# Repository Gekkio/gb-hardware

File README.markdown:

# Game Boy -related custom hardware by gekkio
Licensed under Creative Commons Attribution 4.0 International.

Used libraries:

* [gekkio-kicad-libs](https://github.com/Gekkio/gekkio-kicad-libs)
* [kicad-footprints](https://github.com/KiCad/kicad-footprints)
* [kicad-symbols](https://github.com/KiCad/kicad-symbols)

## License violations (a.k.a Naughty List)

All the designs in this repository are licensed very liberally under CC BY 4.0,
so you can modify and/or sell them commercially if you want. There's just one
requirement: **attribution**

Basically it just means this: don't remove the original creator's name from the
design. [Here's the full description about it in CC BY 4.0](https://creativecommons.org/licenses/by/4.0/#deed-conditions)

Known license violations:

- Ferrante Crafts: While it wasn't fully intentional and they've
  apologised, they took my GB-CART32K-A design, altered the silkscreen to
  include their name while removing all mention of mine, and then sold these
  carts to people for profit

[Don't be this meme!](https://knowyourmeme.com/memes/i-made-this)

## GB-BENCH-G1

Test bench board for 1st generation Game Boy CPUs (DMG-CPU, SGB-CPU).

* PCB size: 100x100mm
* PCB thickness: any
* Layer count: 4
* Surface finish: any

## GB-BRK-CART

Breakout Game Boy cartridge.

* PCB size: 51.4x61mm
* PCB thickness: 1.0mm
* Layer count: 2
* Surface finish: ENIG (absolutely *do not* choose HASL)

[GB-BRK-CART v4.0 Mouser project for easy part shopping](http://www.mouser.com/ProjectManager/ProjectDetail.aspx?AccessID=61700168c3)

## GB-BRK-LINK-A

Breakout board for original Game Boy (DMG) link port.

* PCB size: 30x34mm
* PCB thickness: 1.2mm
* Layer count: 2
* Surface finish: any

## GB-BRK-LINK-B

Breakout board for compact link port used in Game Boy Pocket (MGB) and later.

* PCB size: 30x34mm
* PCB thickness: 1.2mm
* Layer count: 2
* Surface finish: any

## GB-BRK-M-XS

Compact male breakout board for the Game Boy cartridge slot.

* PCB size: 51.4x25mm
* PCB thickness: 1.0mm
* Layer count: 2
* Surface finish: ENIG (absolutely *do not* choose HASL)

## GB-BRK-SLOT-A

Breakout board for original Game Boy (DMG) cartridge slot.

* PCB size: 81x80mm
* PCB thickness: 1.2mm
* Layer count: 2
* Surface finish: any

## GB-BRK-SLOT-B

Breakout board for Super Game Boy (SGB) / Super Game Boy 2 (SGB2) cartridge
slot.

* PCB size: 81x80mm
* PCB thickness: 1.2mm
* Layer count: 2
* Surface finish: any

## GB-LIVE32

32 kB ROM-only rapid development cartridge.

* PCB size: 51.4x61mm
* PCB thickness: 1.0mm
* Layer count: 4
* Surface finish: ENIG (absolutely *do not choose HASL*)

[Firmware + software](https://github.com/Gekkio/gb-live32)

[GB-LIVE32 v2.0 Mouser project for easy part shopping](https://www.mouser.com/ProjectManager/ProjectDetail.aspx?AccessID=16281c67ef)

## GB-CART32K-A

Simple ROM-only flash cartridge for 32kx8 PLCC-32 flash (larger chips up to
512kx8 are supported, but only 32k is usable).

* PCB size: 51.4x61mm
* PCB thickness: 1.0mm
* Layer count: 2
* Surface finish: ENIG (absolutely *do not choose HASL*)

## GB-CART256K-A

Simple ROM-only flash cartridge for 128kx8 / 256kx8 PLCC-32 flash.

* PCB size: 51.4x61mm
* PCB thickness: 1.0mm
* Layer count: 2
* Surface finish: ENIG (absolutely *do not choose HASL*)

[Firmware](https://github.com/Gekkio/gb-cart256k-a)

## GB-BRK-CPU-G1

Breakout board for 1st generation Game Boy CPUs (DMG/SGB).

* PCB size: 80x80mm
* PCB thickness: any
* Layer count: 2
* Surface finish: any

## GB-BRK-CPU-G2

Breakout board for 2nd generation Game Boy CPUs (MGB/SGB2).

* PCB size: 80x80mm
* PCB thickness: any
* Layer count: 2
* Surface finish: any

## GB-BRK-TR-A

Breakout board for original Game Boy (DMG) power board transformer.

* PCB size: 24x35mm
* PCB thickness: any
* Layer count: 2
* Surface finish: any

## GB-MBCTEST

Game Boy MBC (Memory Bank Controller) testing cartridge.

* PCB size: 51.4x61mm
* PCB thickness: 1.0mm
* Layer count: 2
* Surface finish: ENIG (absolutely *do not choose HASL*)

## GB-CARTPP-XC

An eXtra Cheap Game Boy cartridge dumper/flasher based on PIC18F45K50.

* PCB size: 80x55mm
* PCB thickness: any (1.0mm recommended)
* Layer count: 2
* Surface finish: any

## GB-CARTPP-DIY

A Game Boy cartridge dumper/flasher based on PIC18F45K50 with DIY-friendly
parts (big and easy to solder).

* PCB size: 100x100mm
* PCB thickness: any
* Layer count: 2
* Surface finish: any

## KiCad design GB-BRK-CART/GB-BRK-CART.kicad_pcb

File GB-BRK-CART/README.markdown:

# Notes

* The power LED (+ resistor) and the bypass capacitor are optional.
* The value of R1 might be too high to get enough current for the LED and can
  be replaced with a lower value if necessary. The value is set quite high to
  minimize power usage and still works fine with the components I use.
* All parts in the BOM can be replaced with pretty much any similar parts.

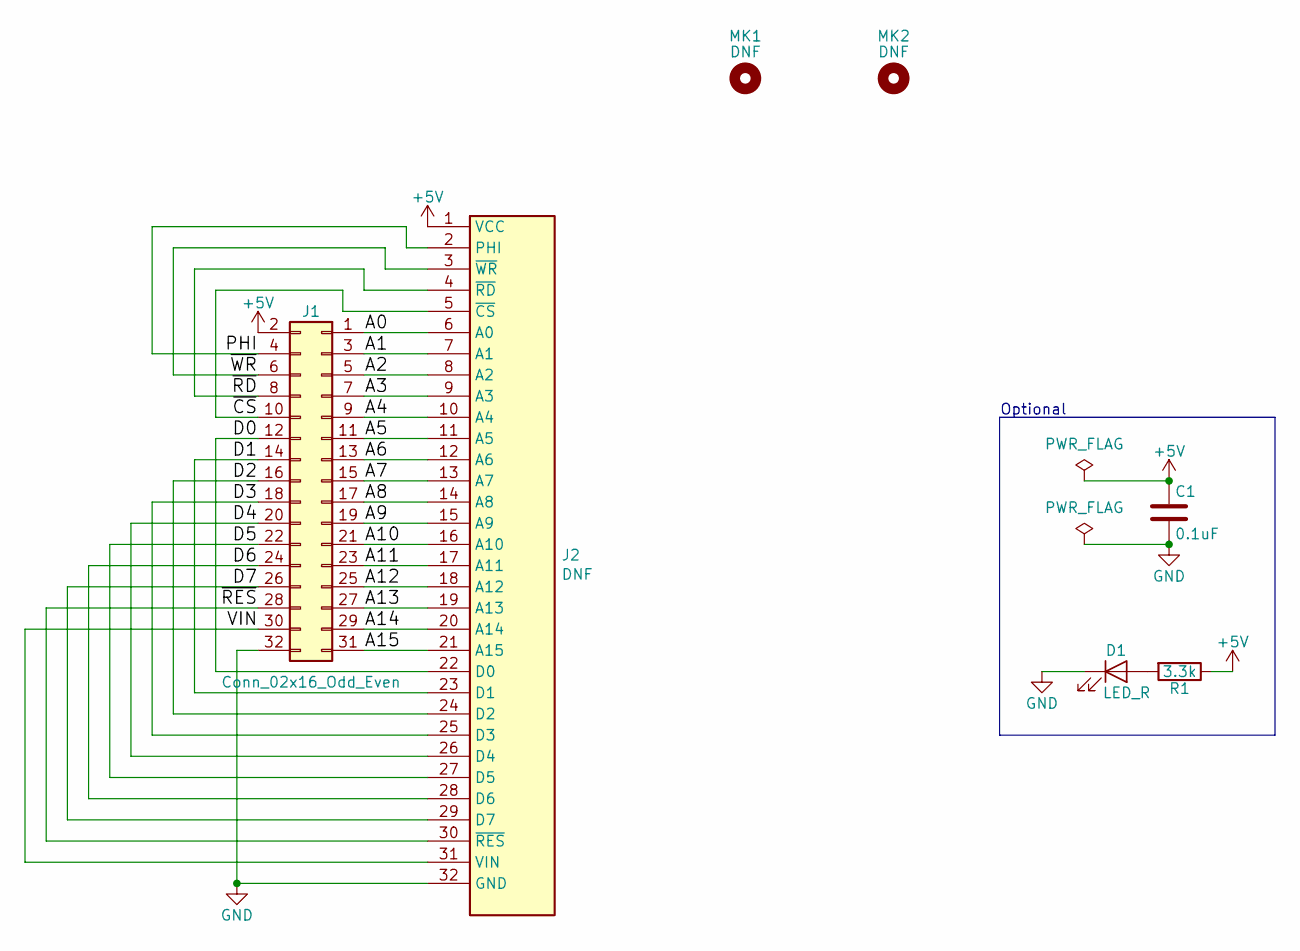
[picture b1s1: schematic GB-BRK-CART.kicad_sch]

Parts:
C1: 0.1uF; C_0603_1608Metric; Rating 16V X5R; MPN 06035C104KAT4A
D1: LED_R; LED_0603_1608Metric; MPN 150060SS75000
J1: Conn_02x16_Odd_Even; PinHeader_2x16_P2.54mm_Vertical_SMD; MPN 15-91-0800
J2: DNF; GameBoy_Cartridge_1x32_P1.50mm_Edge
MK1: DNF; MountingHole_7.2mm
MK2: DNF; MountingHole_2.3mm
R1: 3.3k; R_0603_1608Metric; Rating 1/10W 5%; MPN CRCW06033K30JNEB

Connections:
+5V: C1.1, J1.2, J2.1 (VCC), R1.1
/A0: J1.1, J2.6 (A0)
/A1: J1.3, J2.7 (A1)
/A2: J1.5, J2.8 (A2)
/A3: J1.7, J2.9 (A3)
/A4: J1.9, J2.10 (A4)
/A5: J1.11, J2.11 (A5)
/A6: J1.13, J2.12 (A6)
/A7: J1.15, J2.13 (A7)
/A8: J1.17, J2.14 (A8)
/A9: J1.19, J2.15 (A9)
/A10: J1.21, J2.16 (A10)
/A11: J1.23, J2.17 (A11)
/A12: J1.25, J2.18 (A12)
/A13: J1.27, J2.19 (A13)
/A14: J1.29, J2.20 (A14)
/A15: J1.31, J2.21 (A15)
/D0: J1.12, J2.22 (D0)
/D1: J1.14, J2.23 (D1)
/D2: J1.16, J2.24 (D2)
/D3: J1.18, J2.25 (D3)
/D4: J1.20, J2.26 (D4)
/D5: J1.22, J2.27 (D5)
/D6: J1.24, J2.28 (D6)
/D7: J1.26, J2.29 (D7)
/PHI: J1.4, J2.2 (PHI)
/VIN: J1.30, J2.31 (VIN)
/~CS: J1.10, J2.5 (~CS)
/~RD: J1.8, J2.4 (~RD)
/~RES: J1.28, J2.30 (~RES)
/~WR: J1.6, J2.3 (~WR)
GND: C1.2, D1.1 (K), J1.32, J2.32 (GND)
unnamed: D1.2 (A), R1.2

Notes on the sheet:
Optional

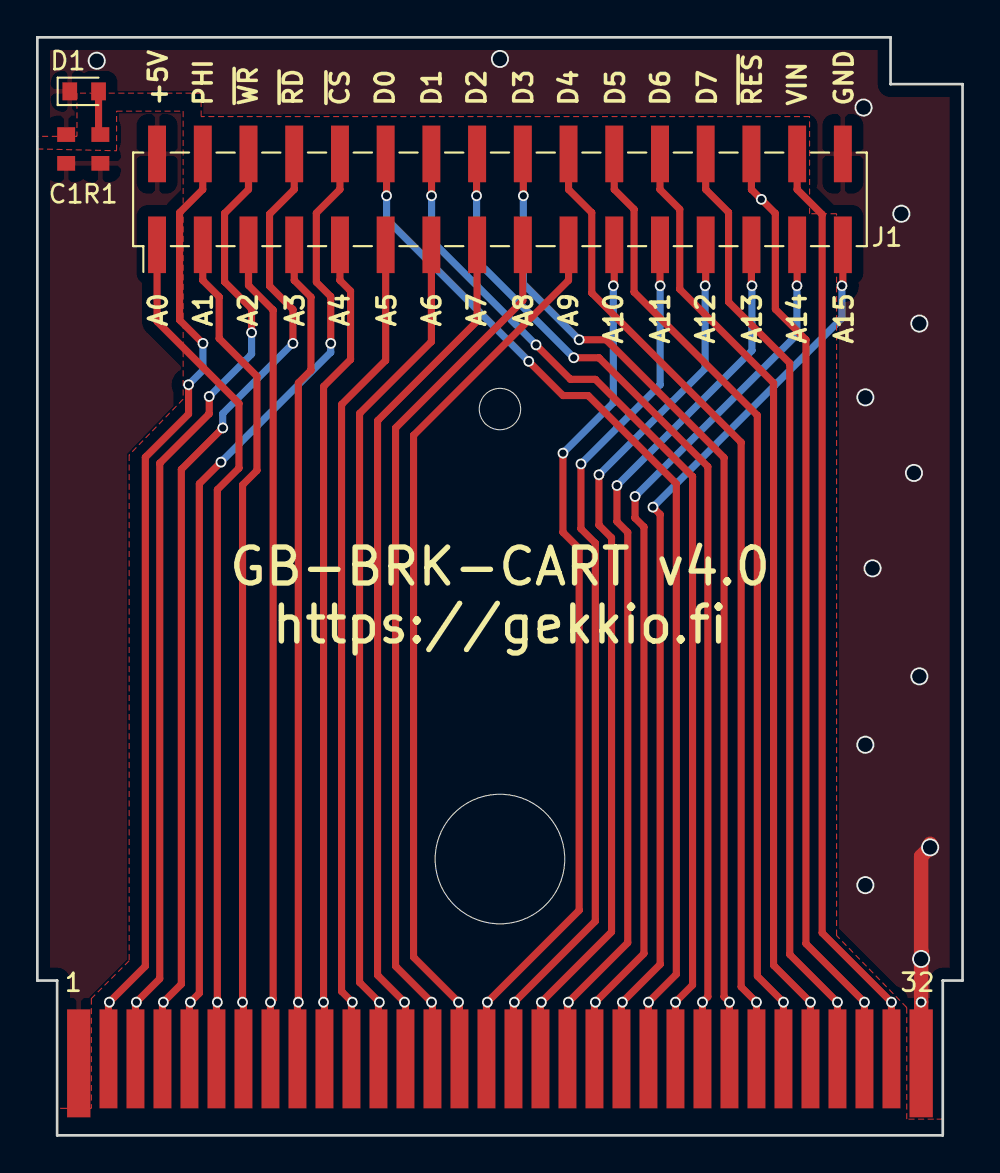
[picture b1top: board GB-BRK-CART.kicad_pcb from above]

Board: 2 copper layers, 51.4 x 61.0 mm, 7 parts (0 on the bottom side), 33 nets.

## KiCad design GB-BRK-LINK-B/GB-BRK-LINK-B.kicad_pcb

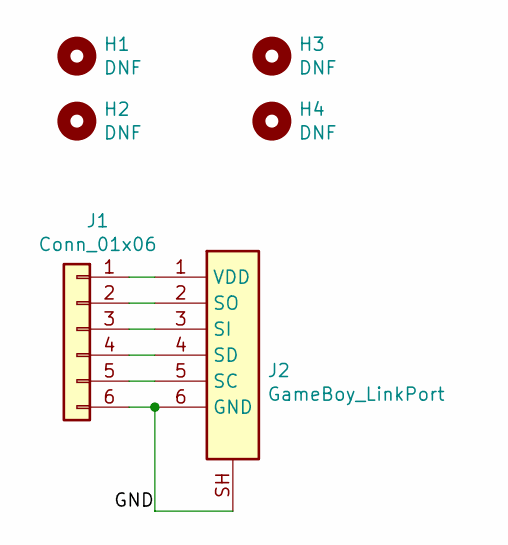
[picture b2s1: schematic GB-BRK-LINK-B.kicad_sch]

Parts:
H1, H2, H3, H4: DNF; MountingHole_3.2mm_M3
J1: Conn_01x06; PinHeader_1x06_P2.54mm_Vertical
J2: GameBoy_LinkPort; GameBoy_LinkPort_MGB_Horizontal

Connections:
/GND: J1.6, J2.6 (GND), J2.SH
unnamed: J1.1, J2.1 (VDD)
unnamed: J1.2, J2.2 (SO)
unnamed: J1.3, J2.3 (SI)
unnamed: J1.4, J2.4 (SD)
unnamed: J1.5, J2.5 (SC)

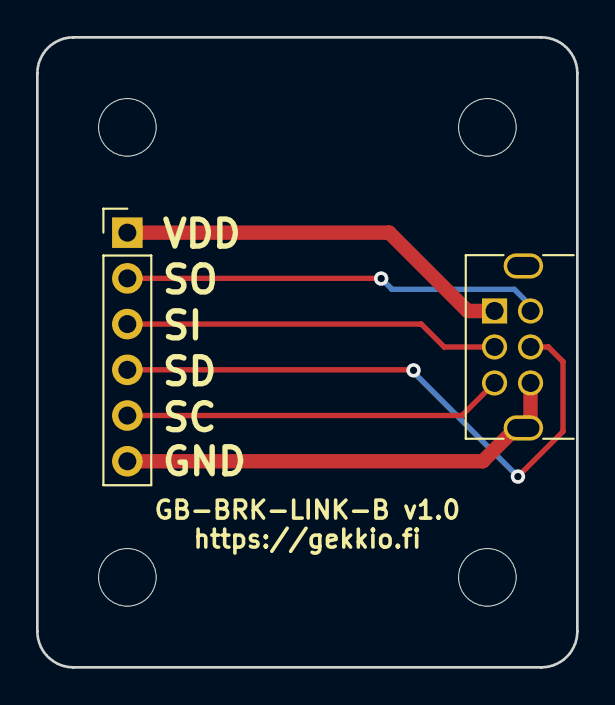
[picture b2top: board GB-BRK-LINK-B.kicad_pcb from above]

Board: 2 copper layers, 30.0 x 35.0 mm, 6 parts (0 on the bottom side), 6 nets.

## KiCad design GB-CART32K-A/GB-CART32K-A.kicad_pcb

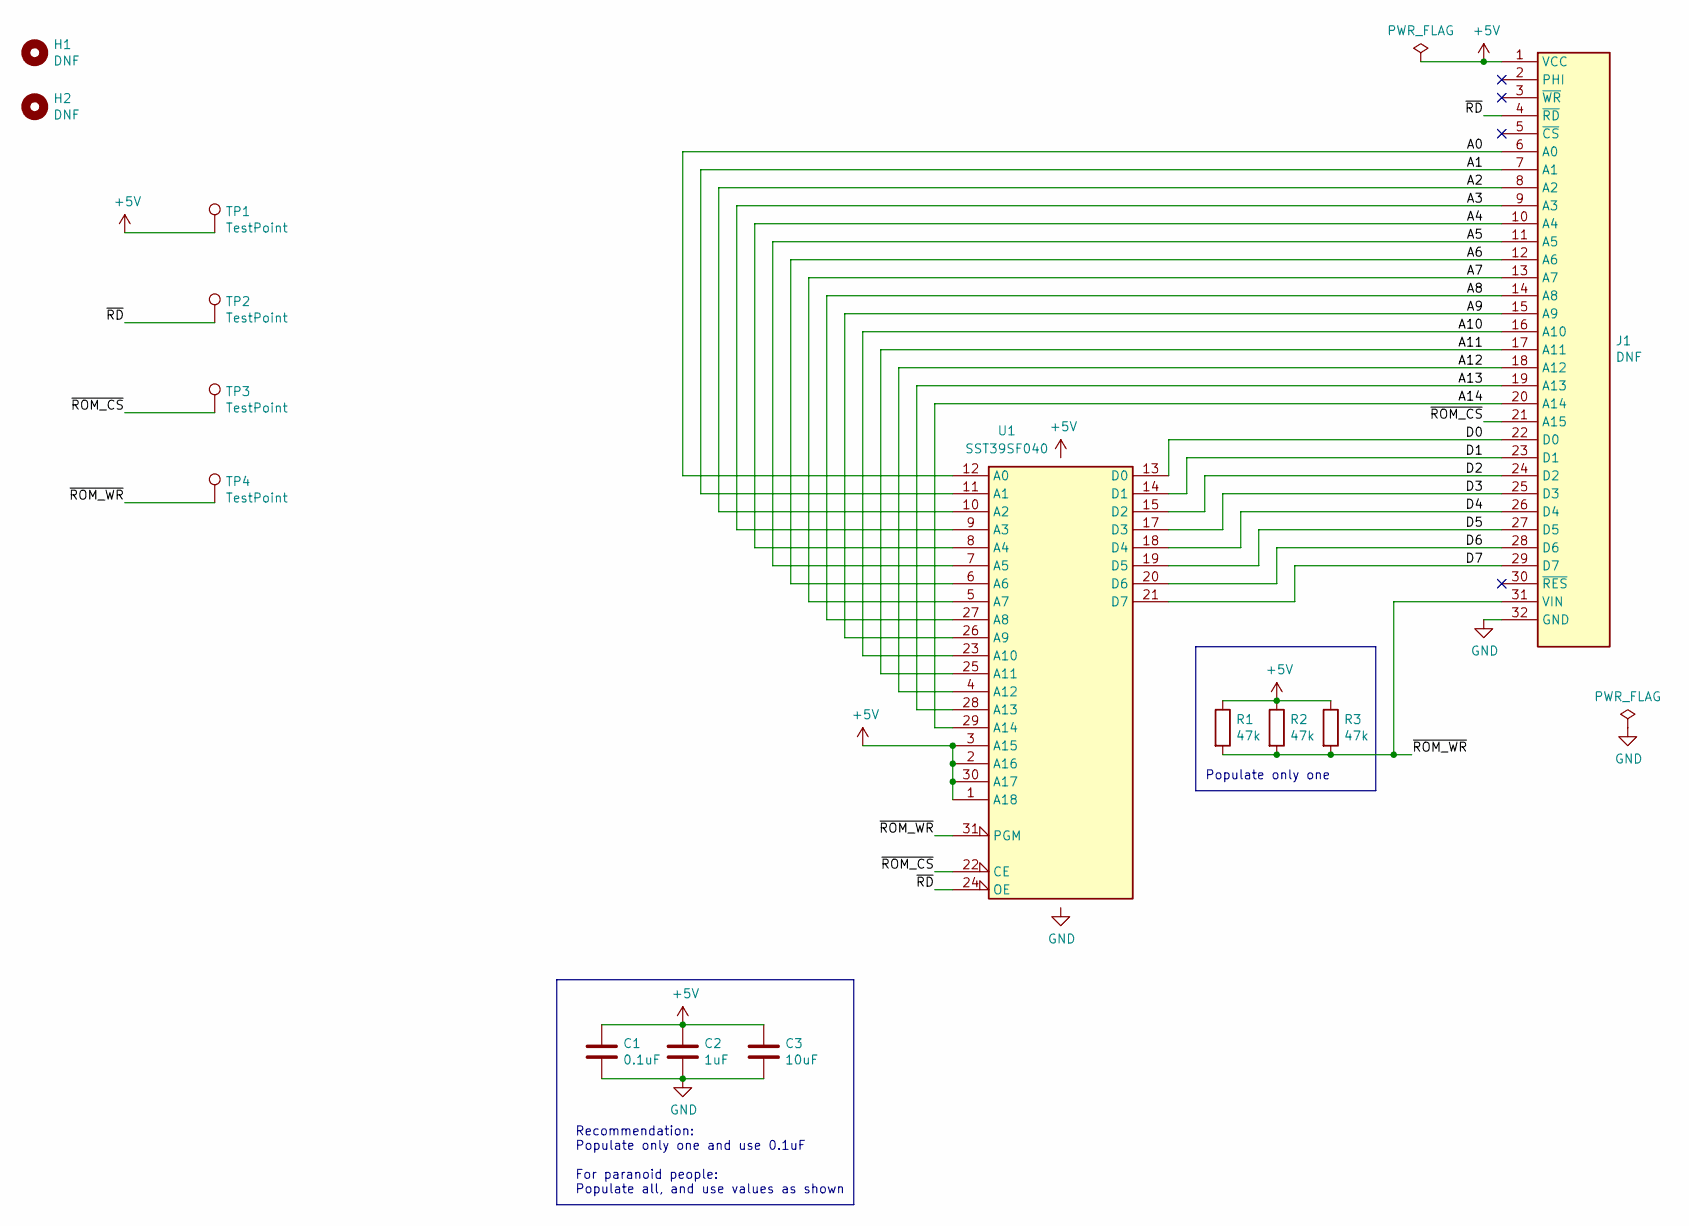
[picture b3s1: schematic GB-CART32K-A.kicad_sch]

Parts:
C1: 0.1uF; C_0603_1608Metric
C2: 1uF; C_0805_2012Metric
C3: 10uF; C_1206_3216Metric
H1: DNF; MountingHole_7.2mm
H2: DNF; MountingHole_2.3mm
J1: DNF; GameBoy_Cartridge_1x32_P1.50mm_Edge
R1: 47k; R_0603_1608Metric
R2: 47k; R_0805_2012Metric
R3: 47k; R_1206_3216Metric
TP1, TP2, TP3, TP4: TestPoint; TestPoint_THTPad_D2.0mm_Drill1.0mm
U1: SST39SF040; PLCC-32_11.4x14.0mm_P1.27mm

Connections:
+5V: C1.1, C2.1, C3.1, J1.1 (VCC), R1.1, R2.1, R3.1, TP1.1, U1.1 (A18), U1.2 (A16), U1.3 (A15), U1.30 (A17), U1.32 (VCC)
/A0: J1.6 (A0), U1.12 (A0)
/A1: J1.7 (A1), U1.11 (A1)
/A2: J1.8 (A2), U1.10 (A2)
/A3: J1.9 (A3), U1.9 (A3)
/A4: J1.10 (A4), U1.8 (A4)
/A5: J1.11 (A5), U1.7 (A5)
/A6: J1.12 (A6), U1.6 (A6)
/A7: J1.13 (A7), U1.5 (A7)
/A8: J1.14 (A8), U1.27 (A8)
/A9: J1.15 (A9), U1.26 (A9)
/A10: J1.16 (A10), U1.23 (A10)
/A11: J1.17 (A11), U1.25 (A11)
/A12: J1.18 (A12), U1.4 (A12)
/A13: J1.19 (A13), U1.28 (A13)
/A14: J1.20 (A14), U1.29 (A14)
/D0: J1.22 (D0), U1.13 (D0)
/D1: J1.23 (D1), U1.14 (D1)
/D2: J1.24 (D2), U1.15 (D2)
/D3: J1.25 (D3), U1.17 (D3)
/D4: J1.26 (D4), U1.18 (D4)
/D5: J1.27 (D5), U1.19 (D5)
/D6: J1.28 (D6), U1.20 (D6)
/D7: J1.29 (D7), U1.21 (D7)
/~RD: J1.4 (~RD), TP2.1, U1.24 (OE)
/~ROM_CS: J1.21 (A15), TP3.1, U1.22 (CE)
/~ROM_WR: J1.31 (VIN), R1.2, R2.2, R3.2, TP4.1, U1.31 (PGM)
GND: C1.2, C2.2, C3.2, J1.32 (GND), U1.16 (GND)

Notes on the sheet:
Recommendation: Populate only one and use 0.1uF For paranoid people: Populate all, and use values as shown
Populate only one

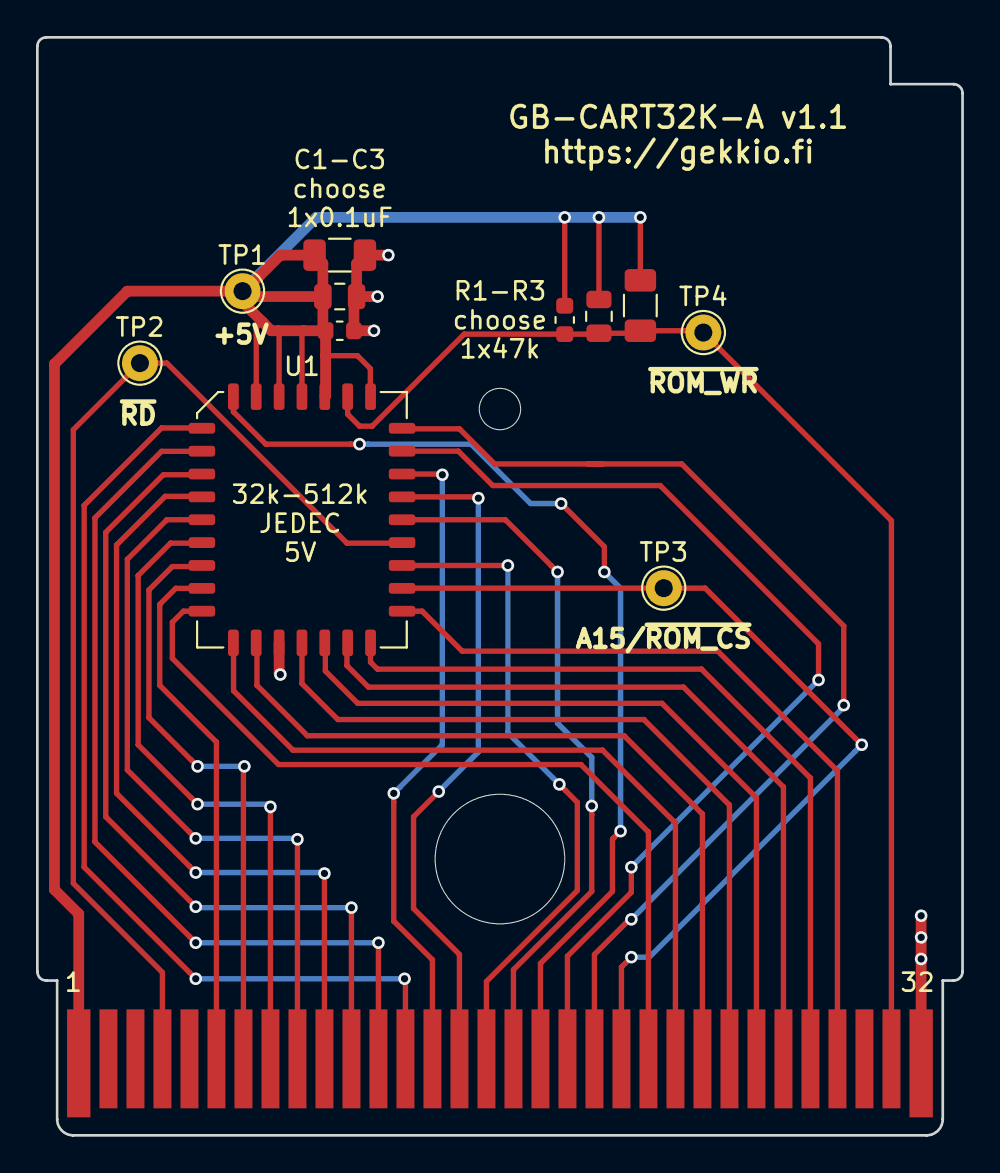
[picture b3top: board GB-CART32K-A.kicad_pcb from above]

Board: 2 copper layers, 51.4 x 61.0 mm, 14 parts (0 on the bottom side), 28 nets.

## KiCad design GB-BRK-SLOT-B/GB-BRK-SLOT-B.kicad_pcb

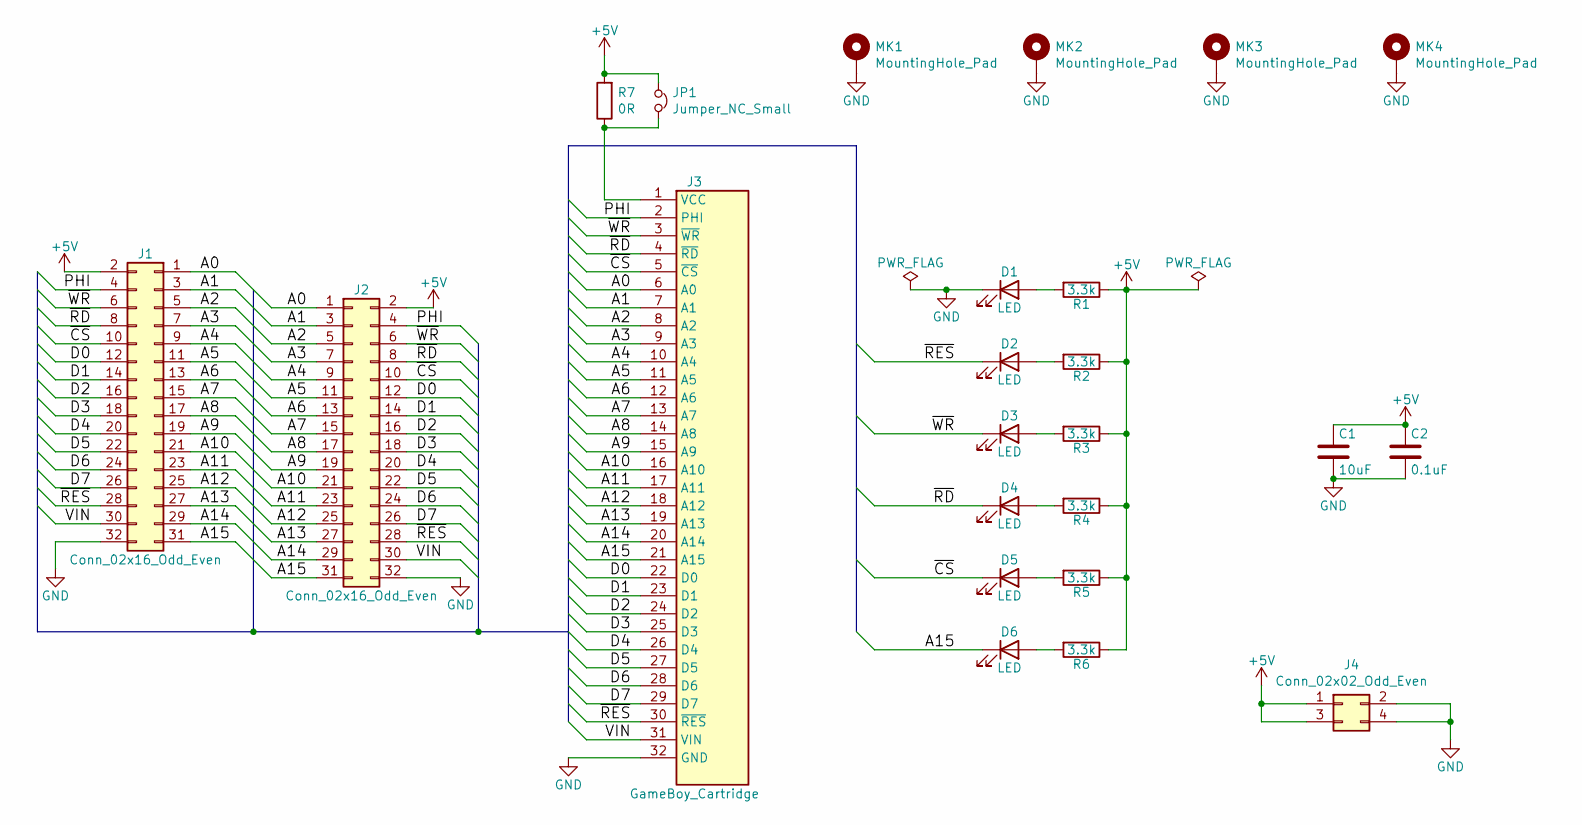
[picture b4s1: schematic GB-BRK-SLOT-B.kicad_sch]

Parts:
C1: 10uF; C_1206_3216Metric
C2: 0.1uF; C_0603_1608Metric
D1, D2, D3, D4, D5, D6: LED; LED_0603_1608Metric
J1: Conn_02x16_Odd_Even; PinSocket_2x16_P2.54mm_Vertical
J2: Conn_02x16_Odd_Even; PinHeader_2x16_P2.54mm_Vertical
J3: GameBoy_Cartridge; GameBoy_Cartridge_SGB-SGB2_1x32_P1.50mm_Socket_Horizontal
J4: Conn_02x02_Odd_Even; PinHeader_2x02_P2.54mm_Vertical
JP1: Jumper_NC_Small; PinHeader_1x02_P2.54mm_Vertical
MK1, MK2, MK3, MK4: MountingHole_Pad; MountingHole_3.2mm_M3_Pad_Via
R1, R2, R3, R4, R5, R6: 3.3k; R_0603_1608Metric
R7: 0R; R_1206_3216Metric_Pad1.42x1.75mm_HandSolder

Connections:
+5V: C1.1, C2.1, J1.2, J2.2, J4.1, J4.3, JP1.1, R1.1, R2.1, R3.1, R4.1, R5.1, R6.1, R7.2
/A0: J1.1, J2.1, J3.6 (A0)
/A1: J1.3, J2.3, J3.7 (A1)
/A2: J1.5, J2.5, J3.8 (A2)
/A3: J1.7, J2.7, J3.9 (A3)
/A4: J1.9, J2.9, J3.10 (A4)
/A5: J1.11, J2.11, J3.11 (A5)
/A6: J1.13, J2.13, J3.12 (A6)
/A7: J1.15, J2.15, J3.13 (A7)
/A8: J1.17, J2.17, J3.14 (A8)
/A9: J1.19, J2.19, J3.15 (A9)
/A10: J1.21, J2.21, J3.16 (A10)
/A11: J1.23, J2.23, J3.17 (A11)
/A12: J1.25, J2.25, J3.18 (A12)
/A13: J1.27, J2.27, J3.19 (A13)
/A14: J1.29, J2.29, J3.20 (A14)
/A15: D6.1 (K), J1.31, J2.31, J3.21 (A15)
/D0: J1.12, J2.12, J3.22 (D0)
/D1: J1.14, J2.14, J3.23 (D1)
/D2: J1.16, J2.16, J3.24 (D2)
/D3: J1.18, J2.18, J3.25 (D3)
/D4: J1.20, J2.20, J3.26 (D4)
/D5: J1.22, J2.22, J3.27 (D5)
/D6: J1.24, J2.24, J3.28 (D6)
/D7: J1.26, J2.26, J3.29 (D7)
/PHI: J1.4, J2.4, J3.2 (PHI)
/VIN: J1.30, J2.30, J3.31 (VIN)
/~CS: D5.1 (K), J1.10, J2.10, J3.5 (~CS)
/~RD: D4.1 (K), J1.8, J2.8, J3.4 (~RD)
/~RES: D2.1 (K), J1.28, J2.28, J3.30 (~RES)
/~WR: D3.1 (K), J1.6, J2.6, J3.3 (~WR)
GND: C1.2, C2.2, D1.1 (K), J1.32, J2.32, J3.32 (GND), J4.2, J4.4, MK1.1, MK2.1, MK3.1, MK4.1
unnamed: D1.2 (A), R1.2
unnamed: D2.2 (A), R2.2
unnamed: D3.2 (A), R3.2
unnamed: D4.2 (A), R4.2
unnamed: D5.2 (A), R5.2
unnamed: D6.2 (A), R6.2
unnamed: J3.1 (VCC), JP1.2, R7.1

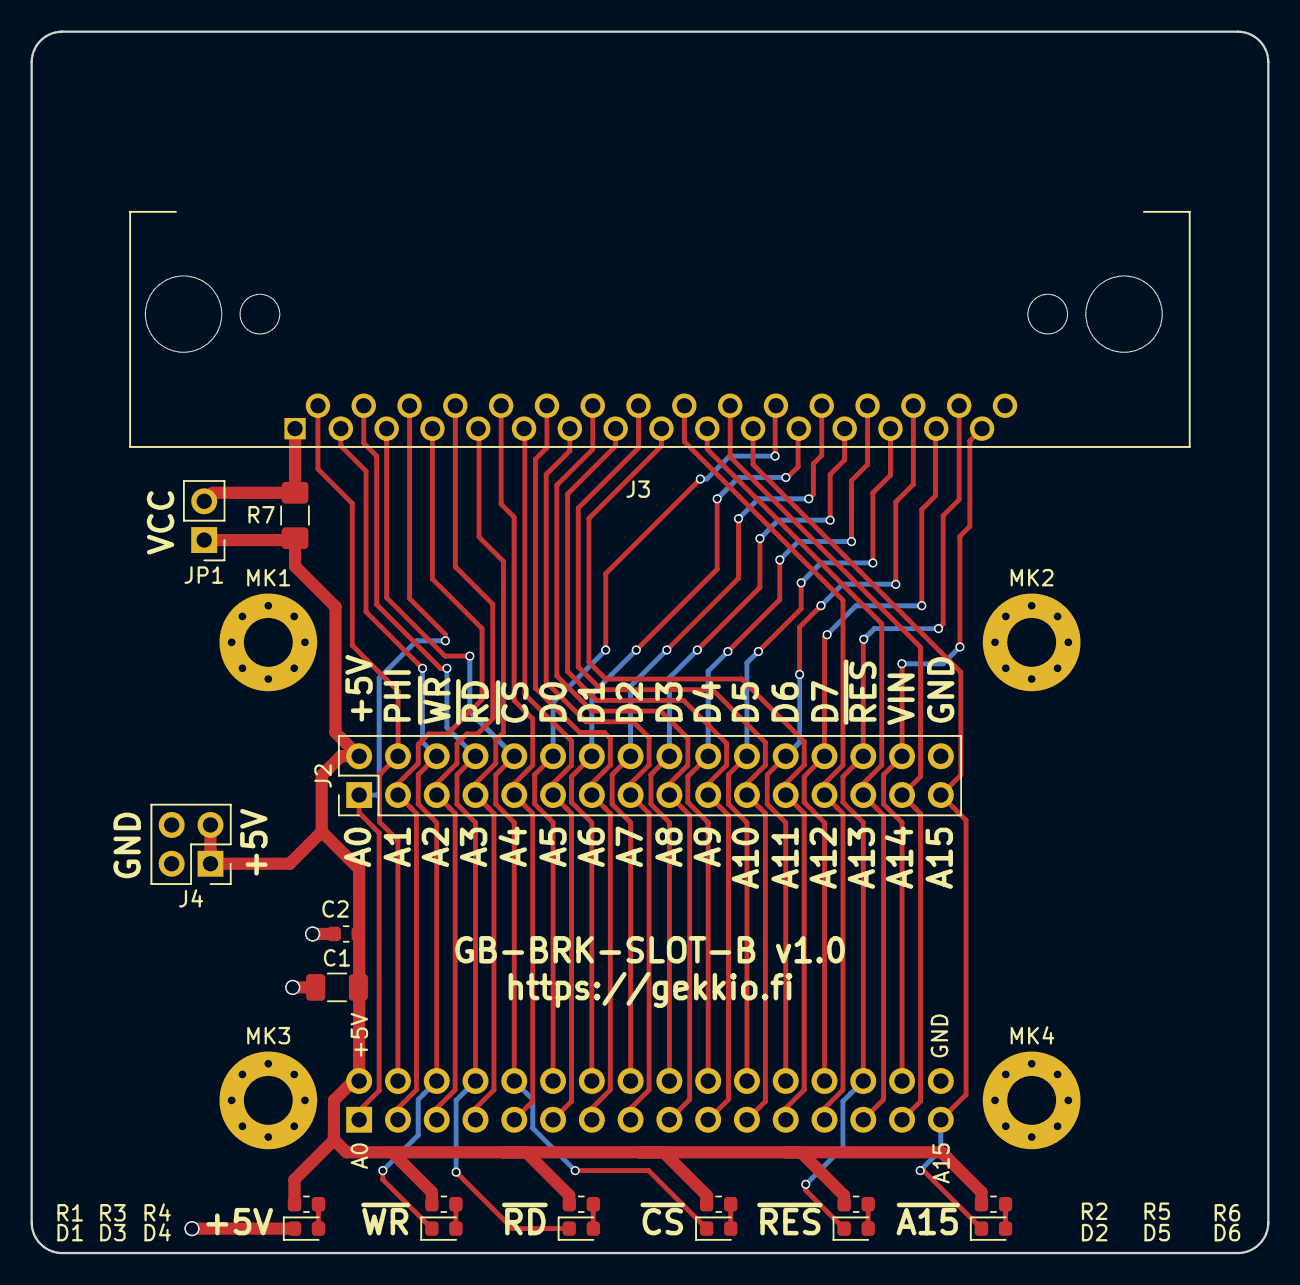
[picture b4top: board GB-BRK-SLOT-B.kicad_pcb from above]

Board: 2 copper layers, 81.0 x 80.0 mm, 24 parts (1 on the bottom side), 39 nets.

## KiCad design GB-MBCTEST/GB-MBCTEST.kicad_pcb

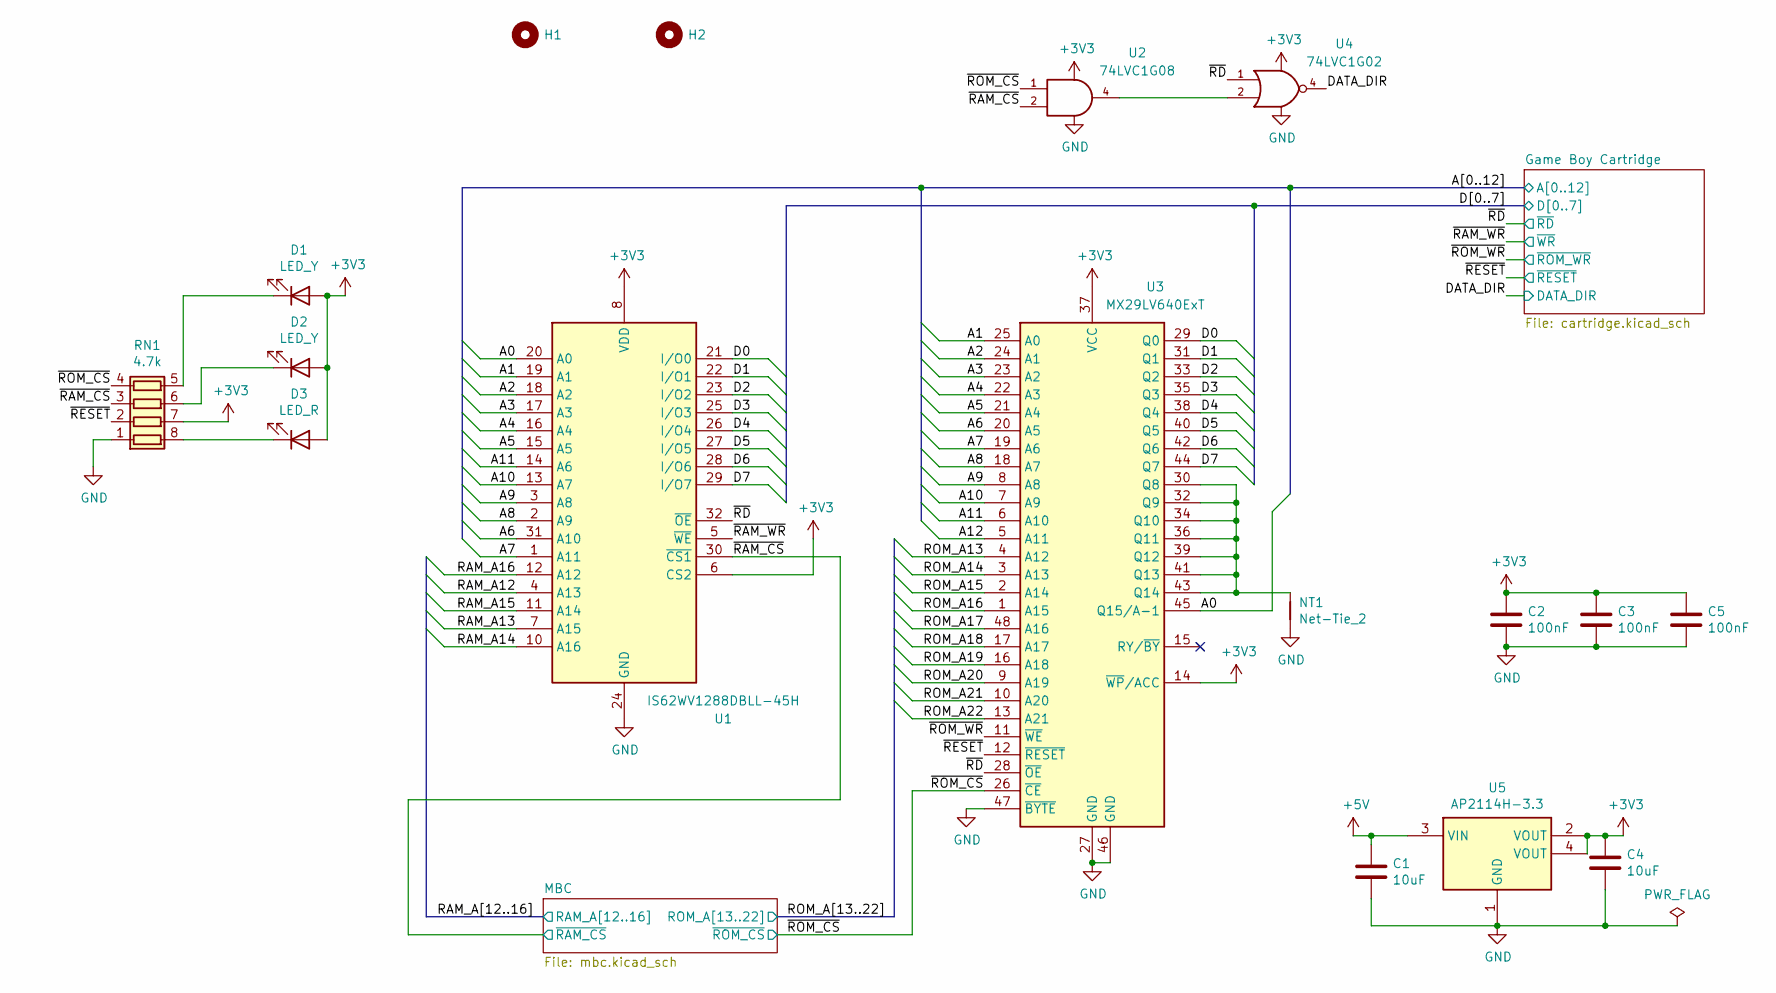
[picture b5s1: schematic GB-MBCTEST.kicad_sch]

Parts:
C1, C4: 10uF; C_1206_3216Metric
C2, C3, C5: 100nF; C_0603_1608Metric
D1, D2: LED_Y; LED_0603_1608Metric
D3: LED_R; LED_0603_1608Metric
H1: DNF; MountingHole_7.2mm
H2: DNF; MountingHole_2.3mm
NT1: Net-Tie_2; NetTie-2_SMD_Pad0.5mm
RN1: 4.7k; R_Array_Convex_4x0603
U1: IS62WV1288DBLL-45H; TSOP-I-32_11.8x8mm_P0.5mm
U2: 74LVC1G08; SOT-353_SC-70-5
U3: MX29LV640ExT; TSOP-I-48_18.4x12mm_P0.5mm
U4: 74LVC1G02; SOT-353_SC-70-5
U5: AP2114H-3.3; SOT-223

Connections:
+3V3: C2.1, C3.1, C4.1, C5.1, D1.2 (A), D2.2 (A), D3.2 (A), RN1.7 (R2.2), U1.6 (CS2), U1.8 (VDD), U2.5 (VCC), U3.14 (~WP/ACC), U3.37 (VCC), U4.5 (VCC), U5.2 (VOUT), U5.4 (VOUT); also elsewhere on the board
+5V: C1.1, U5.3 (VIN); also elsewhere on the board
/A0: U1.20 (A0), U3.45 (Q15/A-1); also elsewhere on the board
/A1: U1.19 (A1), U3.25 (A0); also elsewhere on the board
/A2: U1.18 (A2), U3.24 (A1); also elsewhere on the board
/A3: U1.17 (A3), U3.23 (A2); also elsewhere on the board
/A4: U1.16 (A4), U3.22 (A3); also elsewhere on the board
/A5: U1.15 (A5), U3.21 (A4); also elsewhere on the board
/A6: U1.31 (A10), U3.20 (A5); also elsewhere on the board
/A7: U1.1 (A11), U3.19 (A6); also elsewhere on the board
/A8: U1.2 (A9), U3.18 (A7); also elsewhere on the board
/A9: U1.3 (A8), U3.8 (A8); also elsewhere on the board
/A10: U1.13 (A7), U3.7 (A9); also elsewhere on the board
/A11: U1.14 (A6), U3.6 (A10); also elsewhere on the board
/A12: U3.5 (A11); also elsewhere on the board
/D0: U1.21 (I/O0), U3.29 (Q0); also elsewhere on the board
/D1: U1.22 (I/O1), U3.31 (Q1); also elsewhere on the board
/D2: U1.23 (I/O2), U3.33 (Q2); also elsewhere on the board
/D3: U1.25 (I/O3), U3.35 (Q3); also elsewhere on the board
/D4: U1.26 (I/O4), U3.38 (Q4); also elsewhere on the board
/D5: U1.27 (I/O5), U3.40 (Q5); also elsewhere on the board
/D6: U1.28 (I/O6), U3.42 (Q6); also elsewhere on the board
/D7: U1.29 (I/O7), U3.44 (Q7); also elsewhere on the board
/DATA_DIR: U4.4; also elsewhere on the board
/RAM_A12: U1.4 (A13); also elsewhere on the board
/RAM_A13: U1.7 (A15); also elsewhere on the board
/RAM_A14: U1.10 (A16); also elsewhere on the board
/RAM_A15: U1.11 (A14); also elsewhere on the board
/RAM_A16: U1.12 (A12); also elsewhere on the board
/ROM_A13: U3.4 (A12); also elsewhere on the board
/ROM_A14: U3.3 (A13); also elsewhere on the board
/ROM_A15: U3.2 (A14); also elsewhere on the board
/ROM_A16: U3.1 (A15); also elsewhere on the board
/ROM_A17: U3.48 (A16); also elsewhere on the board
/ROM_A18: U3.17 (A17); also elsewhere on the board
/ROM_A19: U3.16 (A18); also elsewhere on the board
/ROM_A20: U3.9 (A19); also elsewhere on the board
/ROM_A21: U3.10 (A20); also elsewhere on the board
/ROM_A22: U3.13 (A21); also elsewhere on the board
/~RAM_CS: RN1.3 (R3.1), U1.30 (~CS1), U2.2; also elsewhere on the board
/~RAM_WR: U1.5 (~WE); also elsewhere on the board
/~RD: U1.32 (~OE), U3.28 (~OE), U4.1; also elsewhere on the board
/~RESET: RN1.2 (R2.1), U3.12 (~RESET); also elsewhere on the board
/~ROM_CS: RN1.4 (R4.1), U2.1, U3.26 (~CE); also elsewhere on the board
/~ROM_WR: U3.11 (~WE); also elsewhere on the board
GND: C1.2, C2.2, C3.2, C4.2, C5.2, NT1.2, RN1.1 (R1.1), U1.24 (GND), U2.3 (GND), U3.27 (GND), U3.46 (GND), U3.47 (~BYTE), U4.3 (GND), U5.1 (GND); also elsewhere on the board
unnamed: D1.1 (K), RN1.5 (R4.2)
unnamed: D2.1 (K), RN1.6 (R3.2)
unnamed: D3.1 (K), RN1.8 (R1.2)
unnamed: NT1.1, U3.30 (Q8), U3.32 (Q9), U3.34 (Q10), U3.36 (Q11), U3.39 (Q12), U3.41 (Q13), U3.43 (Q14)
unnamed: U2.4, U4.2

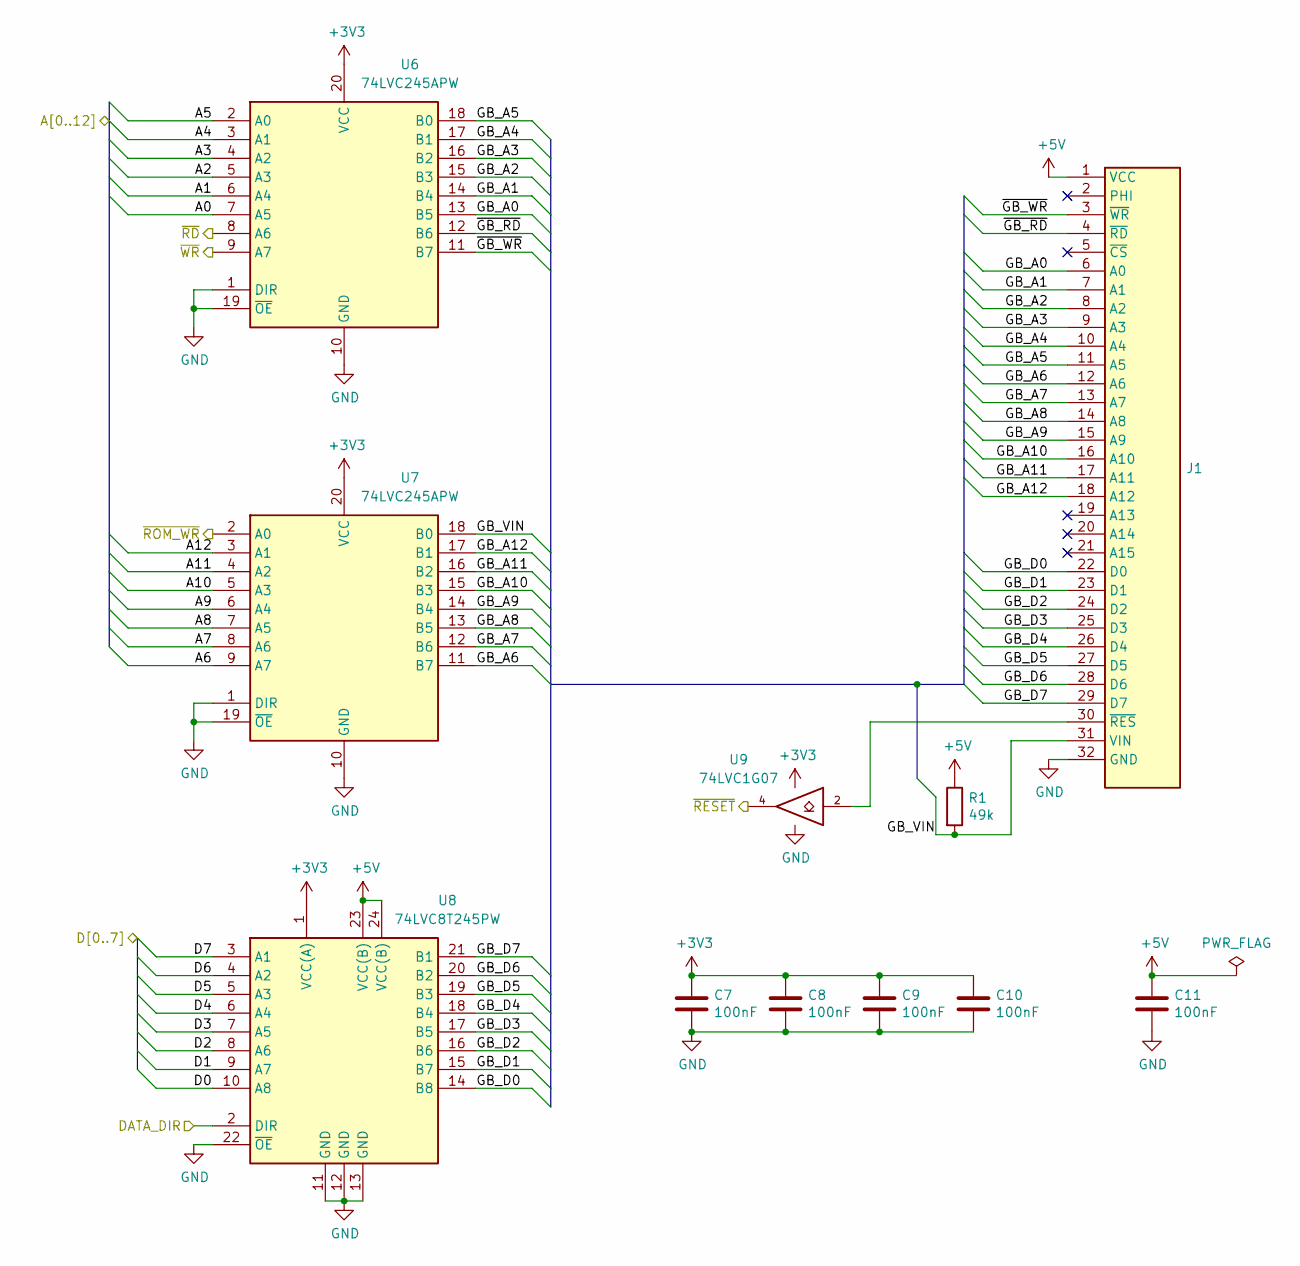
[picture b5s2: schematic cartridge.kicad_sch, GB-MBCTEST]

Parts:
C7, C8, C9, C10, C11: 100nF; C_0603_1608Metric
J1: DNF; GameBoy_Cartridge_1x32_P1.50mm_Edge
R1: 49k; R_0603_1608Metric
U6, U7: 74LVC245APW; TSSOP-20_4.4x6.5mm_P0.65mm
U8: 74LVC8T245PW; TSSOP-24_4.4x7.8mm_P0.65mm
U9: 74LVC1G07; SOT-353_SC-70-5

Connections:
+3V3: C7.1, C8.1, C9.1, C10.1, U6.20 (VCC), U7.20 (VCC), U8.1 (VCC(A)), U9.5 (VCC); also elsewhere on the board
+5V: C11.1, J1.1 (VCC), R1.1, U8.23 (VCC(B)), U8.24 (VCC(B)); also elsewhere on the board
/A0: U6.7 (A5); also elsewhere on the board
/A1: U6.6 (A4); also elsewhere on the board
/A2: U6.5 (A3); also elsewhere on the board
/A3: U6.4 (A2); also elsewhere on the board
/A4: U6.3 (A1); also elsewhere on the board
/A5: U6.2 (A0); also elsewhere on the board
/A6: U7.9 (A7); also elsewhere on the board
/A7: U7.8 (A6); also elsewhere on the board
/A8: U7.7 (A5); also elsewhere on the board
/A9: U7.6 (A4); also elsewhere on the board
/A10: U7.5 (A3); also elsewhere on the board
/A11: U7.4 (A2); also elsewhere on the board
/A12: U7.3 (A1); also elsewhere on the board
/D0: U8.10 (A8); also elsewhere on the board
/D1: U8.9 (A7); also elsewhere on the board
/D2: U8.8 (A6); also elsewhere on the board
/D3: U8.7 (A5); also elsewhere on the board
/D4: U8.6 (A4); also elsewhere on the board
/D5: U8.5 (A3); also elsewhere on the board
/D6: U8.4 (A2); also elsewhere on the board
/D7: U8.3 (A1); also elsewhere on the board
/DATA_DIR: U8.2 (DIR); also elsewhere on the board
/Game Boy Cartridge/GB_A0: J1.6 (A0), U6.13 (B5)
/Game Boy Cartridge/GB_A1: J1.7 (A1), U6.14 (B4)
/Game Boy Cartridge/GB_A2: J1.8 (A2), U6.15 (B3)
/Game Boy Cartridge/GB_A3: J1.9 (A3), U6.16 (B2)
/Game Boy Cartridge/GB_A4: J1.10 (A4), U6.17 (B1)
/Game Boy Cartridge/GB_A5: J1.11 (A5), U6.18 (B0)
/Game Boy Cartridge/GB_A6: J1.12 (A6), U7.11 (B7)
/Game Boy Cartridge/GB_A7: J1.13 (A7), U7.12 (B6)
/Game Boy Cartridge/GB_A8: J1.14 (A8), U7.13 (B5)
/Game Boy Cartridge/GB_A9: J1.15 (A9), U7.14 (B4)
/Game Boy Cartridge/GB_A10: J1.16 (A10), U7.15 (B3)
/Game Boy Cartridge/GB_A11: J1.17 (A11), U7.16 (B2)
/Game Boy Cartridge/GB_A12: J1.18 (A12), U7.17 (B1)
/Game Boy Cartridge/GB_D0: J1.22 (D0), U8.14 (B8)
/Game Boy Cartridge/GB_D1: J1.23 (D1), U8.15 (B7)
/Game Boy Cartridge/GB_D2: J1.24 (D2), U8.16 (B6)
/Game Boy Cartridge/GB_D3: J1.25 (D3), U8.17 (B5)
/Game Boy Cartridge/GB_D4: J1.26 (D4), U8.18 (B4)
/Game Boy Cartridge/GB_D5: J1.27 (D5), U8.19 (B3)
/Game Boy Cartridge/GB_D6: J1.28 (D6), U8.20 (B2)
/Game Boy Cartridge/GB_D7: J1.29 (D7), U8.21 (B1)
/Game Boy Cartridge/GB_VIN: J1.31 (VIN), R1.2, U7.18 (B0)
/Game Boy Cartridge/~GB_RD: J1.4 (~RD), U6.12 (B6)
/Game Boy Cartridge/~GB_WR: J1.3 (~WR), U6.11 (B7)
/~RAM_WR: U6.9 (A7); also elsewhere on the board
/~RD: U6.8 (A6); also elsewhere on the board
/~RESET: U9.4; also elsewhere on the board
/~ROM_WR: U7.2 (A0); also elsewhere on the board
GND: C7.2, C8.2, C9.2, C10.2, C11.2, J1.32 (GND), U6.1 (DIR), U6.10 (GND), U6.19 (~OE), U7.1 (DIR), U7.10 (GND), U7.19 (~OE), U8.11 (GND), U8.12 (GND), U8.13 (GND), U8.22 (~OE), U9.3 (GND); also elsewhere on the board
unnamed: J1.30 (~RES), U9.2
